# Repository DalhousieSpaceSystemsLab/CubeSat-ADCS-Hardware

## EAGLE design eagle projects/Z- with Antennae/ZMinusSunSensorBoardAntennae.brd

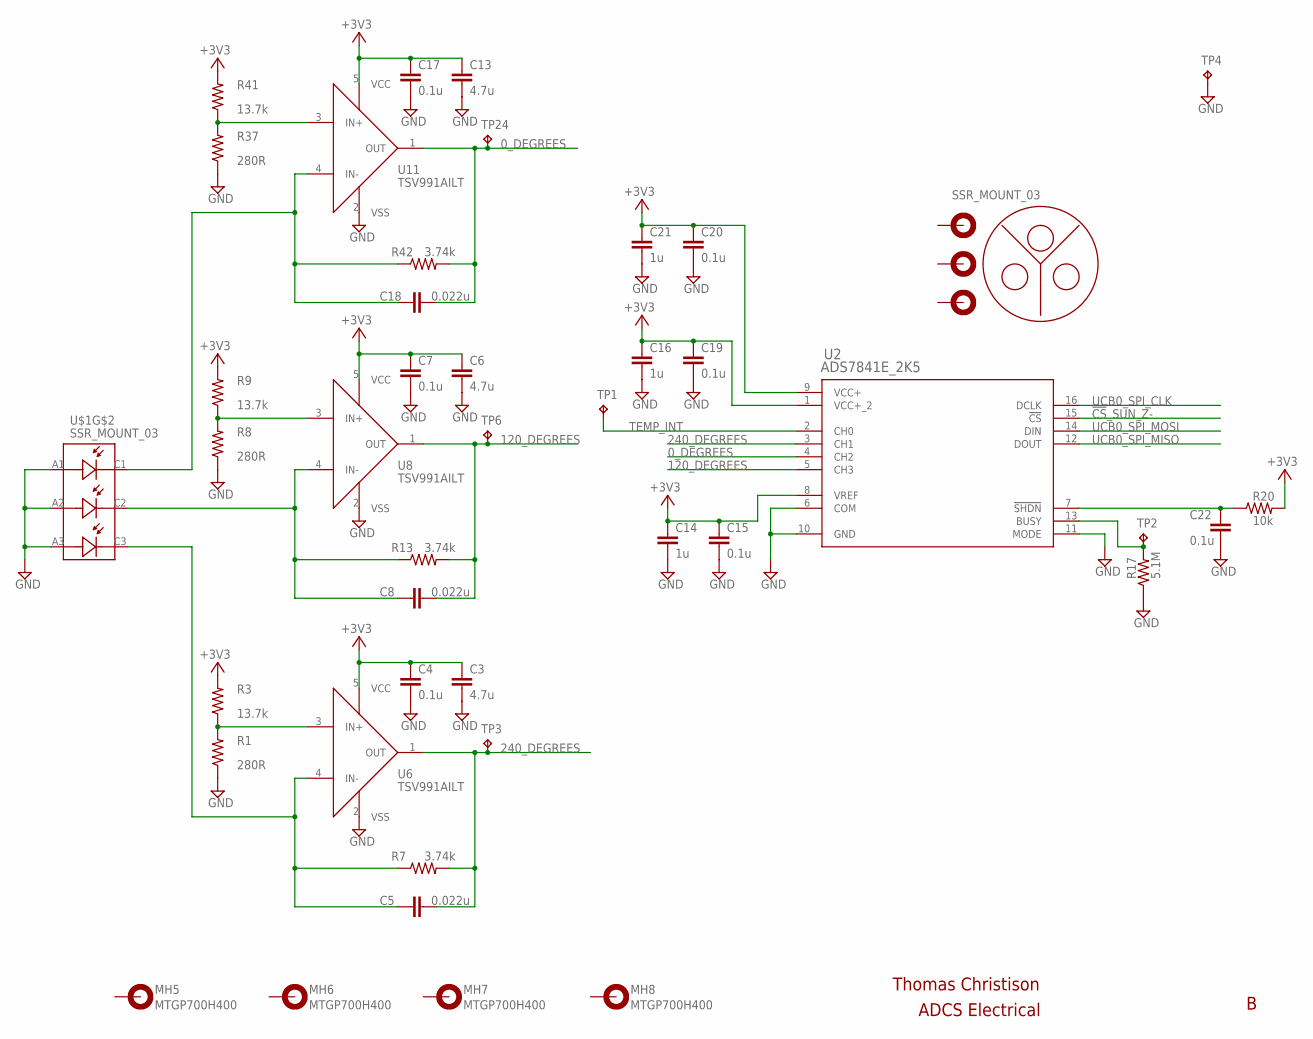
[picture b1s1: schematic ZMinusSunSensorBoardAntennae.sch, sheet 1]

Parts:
C3, C6, C13: 4.7u; C0805
C4, C7, C15, C17, C19, C20, C22: 0.1u; C0402
C5, C8, C18: 0.022u; C0402
C14, C16, C21: 1u; C0402
MH5, MH6, MH7, MH8: MTGP700H400
R1, R8, R37: 280R; R0402
R3, R9, R41: 13.7k; R0402
R7, R13, R42: 3.74k; R0402
R17: 5.1M; R0402
R20: 10k; R0402
TP1, TP2, TP3, TP4, TP6, TP24: TESTPOINT; TP_P76H50
U2: ADS7841E_2K5; DBQ16
U6, U8, U11: TSV991AILT; SOT95P280X145-5N
U$1: SSR_MOUNT_03

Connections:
0_DEGREES: C18.2, R42.2, TP24.1, U2.4 (CH2), U11.1 (OUT)
120_DEGREES: C8.2, R13.2, TP6.1, U2.5 (CH3), U8.1 (OUT)
240_DEGREES: C5.2, R7.2, TP3.1, U2.3 (CH1), U6.1 (OUT)
!CS!_SUN_Z-: U2.15 (!CS); also elsewhere on the board
+3V3: C3.1, C4.1, C6.1, C7.1, C13.1, C14.1, C15.1, C16.1, C17.1, C19.1, C20.1, C21.1, R3.2, R9.2, R20.2, R41.2, U2.1 (VCC+_2), U2.8 (VREF), U2.9 (VCC+), U6.5 (VCC), U8.5 (VCC), U11.5 (VCC); also elsewhere on the board
GND: C3.2, C4.2, C6.2, C7.2, C13.2, C14.2, C15.2, C16.2, C17.2, C19.2, C20.2, C21.2, C22.2, R1.1, R8.1, R17.1, R37.1, TP4.1, U2.6 (COM), U2.10 (GND), U2.11 (MODE), U6.2 (VSS), U8.2 (VSS), U11.2 (VSS), U$1.A1, U$1.A2, U$1.A3; also elsewhere on the board
unnamed: R17.2, TP2.1, U2.13 (BUSY)
unnamed: R1.2, R3.1, U6.3 (IN+)
unnamed: C5.1, R7.1, U6.4 (IN-), U$1.C3
unnamed: C22.1, R20.1, U2.7 (!SHDN)
unnamed: C8.1, R13.1, U8.4 (IN-), U$1.C2
unnamed: R8.2, R9.1, U8.3 (IN+)
unnamed: C18.1, R42.1, U11.4 (IN-), U$1.C1
unnamed: R37.2, R41.1, U11.3 (IN+)
TEMP_INT: TP1.1, U2.2 (CH0); also elsewhere on the board
UCB0_SPI_CLK: U2.16 (DCLK); also elsewhere on the board
UCB0_SPI_MISO: U2.12 (DOUT); also elsewhere on the board
UCB0_SPI_MOSI: U2.14 (DIN); also elsewhere on the board

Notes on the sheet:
Thomas Christison
ADCS Electrical

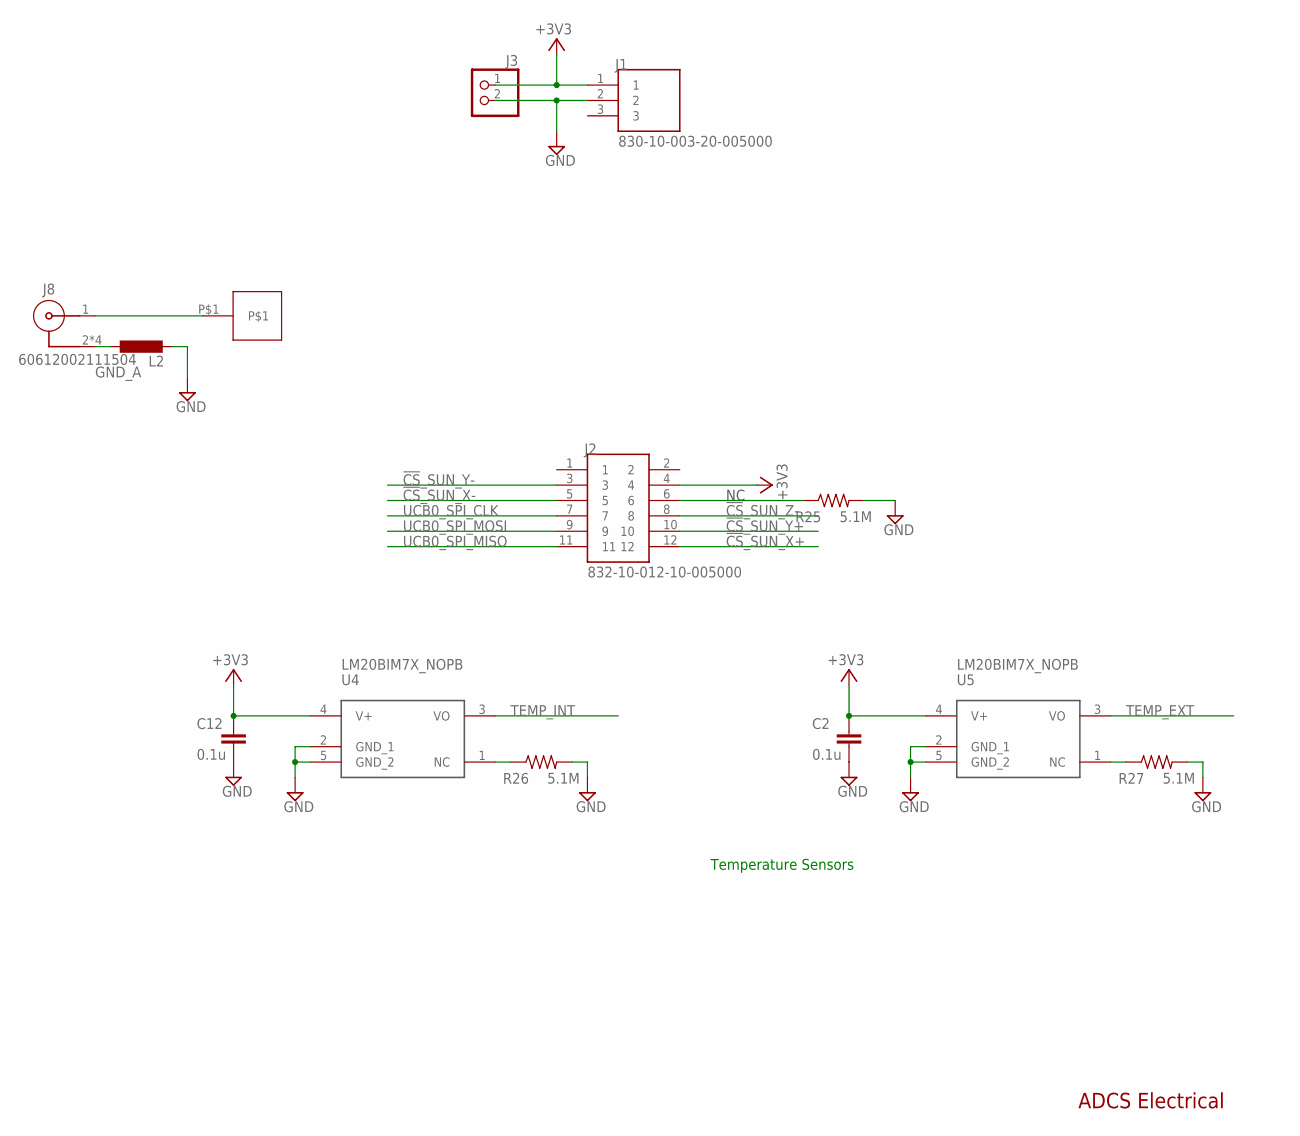
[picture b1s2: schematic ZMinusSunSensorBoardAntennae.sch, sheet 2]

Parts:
C2, C12: 0.1u; C0402
J1: 830-10-003-20-005000
J2: 832-10-012-10-005000
J3: HDR_1X2_; 1X02
J8: 60612002111504
L2: L-EUL5650M; L5650M
R25, R26, R27: 5.1M; R0402
U4, U5: LM20BIM7X_NOPB; SOT23-5P65_210X110L40X22N_LM20
U$2: 2088900001

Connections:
!CS!_SUN_X+: J2.12; also elsewhere on the board
!CS!_SUN_X-: J2.5; also elsewhere on the board
!CS!_SUN_Y+: J2.10; also elsewhere on the board
!CS!_SUN_Y-: J2.3; also elsewhere on the board
!CS!_SUN_Z-: J2.8; also elsewhere on the board
+3V3: C2.1, C12.1, J1.1, J2.4, J3.1, U4.4 (V+), U5.4 (V+); also elsewhere on the board
GND: C2.2, C12.2, J1.2, J3.2, L2.2, R25.2, R26.2, R27.2, U4.2 (GND_1), U4.5 (GND_2), U5.2 (GND_1), U5.5 (GND_2); also elsewhere on the board
GND_A: J8.2, J8.3 (2), J8.4 (2), J8.5 (2), L2.1
unnamed: R26.1, U4.1 (NC)
unnamed: J8.1, U$2.P$1
unnamed: R27.1, U5.1 (NC)
unnamed: J2.6, R25.1
TEMP_EXT: U5.3 (VO); also elsewhere on the board
TEMP_INT: U4.3 (VO); also elsewhere on the board
UCB0_SPI_CLK: J2.7; also elsewhere on the board
UCB0_SPI_MISO: J2.11; also elsewhere on the board
UCB0_SPI_MOSI: J2.9; also elsewhere on the board

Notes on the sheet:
Temperature Sensors
ADCS Electrical

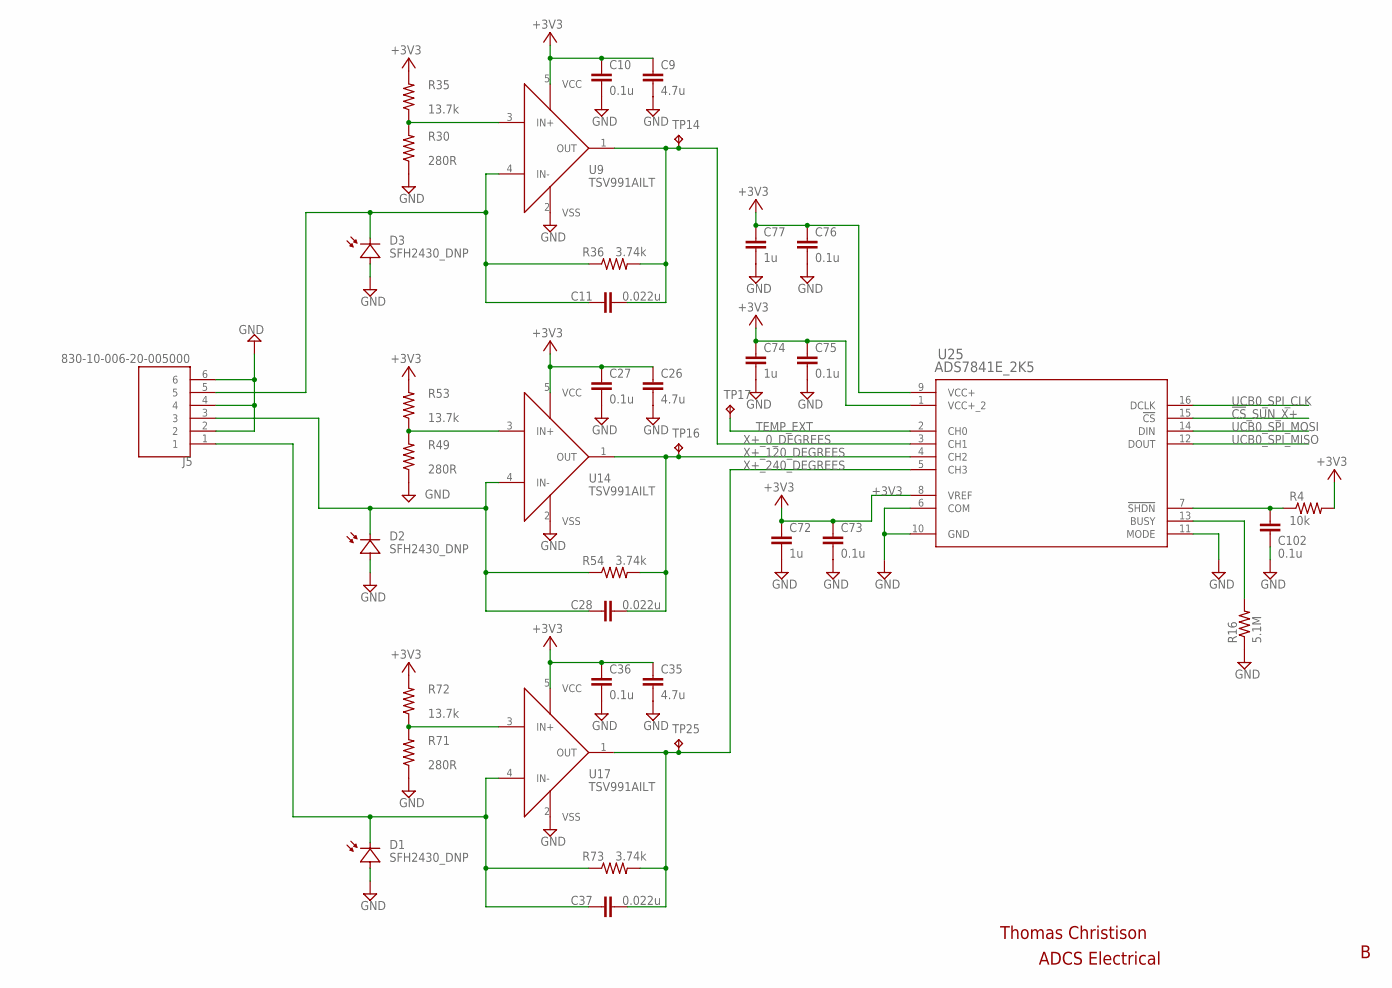
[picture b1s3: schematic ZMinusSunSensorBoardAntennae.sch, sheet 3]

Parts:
C9, C26, C35: 4.7u; C0805
C10, C27, C36, C73, C75, C76, C102: 0.1u; C0402
C11, C28, C37: 0.022u; C0402
C72, C74, C77: 1u; C0402
J5: 830-10-006-20-005000
R4: 10k; R0402
R16: 5.1M; R0402
R30, R49, R71: 280R; R0402
R35, R53, R72: 13.7k; R0402
R36, R54, R73: 3.74k; R0402
TP14, TP16, TP17, TP25: TESTPOINT; TP_P76H50
U9, U14, U17: TSV991AILT; SOT95P280X145-5N
U25: ADS7841E_2K5; DBQ16

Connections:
!CS!_SUN_X+: U25.15 (!CS); also elsewhere on the board
+3V3: C9.1, C10.1, C26.1, C27.1, C35.1, C36.1, C72.1, C73.1, C74.1, C75.1, C76.1, C77.1, R4.2, R35.2, R53.2, R72.2, U9.5 (VCC), U14.5 (VCC), U17.5 (VCC), U25.1 (VCC+_2), U25.8 (VREF), U25.9 (VCC+); also elsewhere on the board
GND: C9.2, C10.2, C26.2, C27.2, C35.2, C36.2, C72.2, C73.2, C74.2, C75.2, C76.2, C77.2, C102.2, J5.2, J5.4, J5.6, R16.1, R30.1, R49.1, R71.1, U9.2 (VSS), U14.2 (VSS), U17.2 (VSS), U25.6 (COM), U25.10 (GND), U25.11 (MODE); also elsewhere on the board
unnamed: C102.1, R4.1, U25.7 (!SHDN)
unnamed: R30.2, R35.1, U9.3 (IN+)
unnamed: C11.1, J5.5, R36.1, U9.4 (IN-)
unnamed: R16.2, U25.13 (BUSY)
unnamed: C28.1, J5.3, R54.1, U14.4 (IN-)
unnamed: C37.1, J5.1, R73.1, U17.4 (IN-)
unnamed: R49.2, R53.1, U14.3 (IN+)
unnamed: R71.2, R72.1, U17.3 (IN+)
TEMP_EXT: TP17.1, U25.2 (CH0); also elsewhere on the board
UCB0_SPI_CLK: U25.16 (DCLK); also elsewhere on the board
UCB0_SPI_MISO: U25.12 (DOUT); also elsewhere on the board
UCB0_SPI_MOSI: U25.14 (DIN); also elsewhere on the board
X+_0_DEGREES: C11.2, R36.2, TP14.1, U9.1 (OUT), U25.3 (CH1)
X+_120_DEGREES: C28.2, R54.2, TP16.1, U14.1 (OUT), U25.4 (CH2)
X+_240_DEGREES: C37.2, R73.2, TP25.1, U17.1 (OUT), U25.5 (CH3)

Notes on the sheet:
Thomas Christison
ADCS Electrical

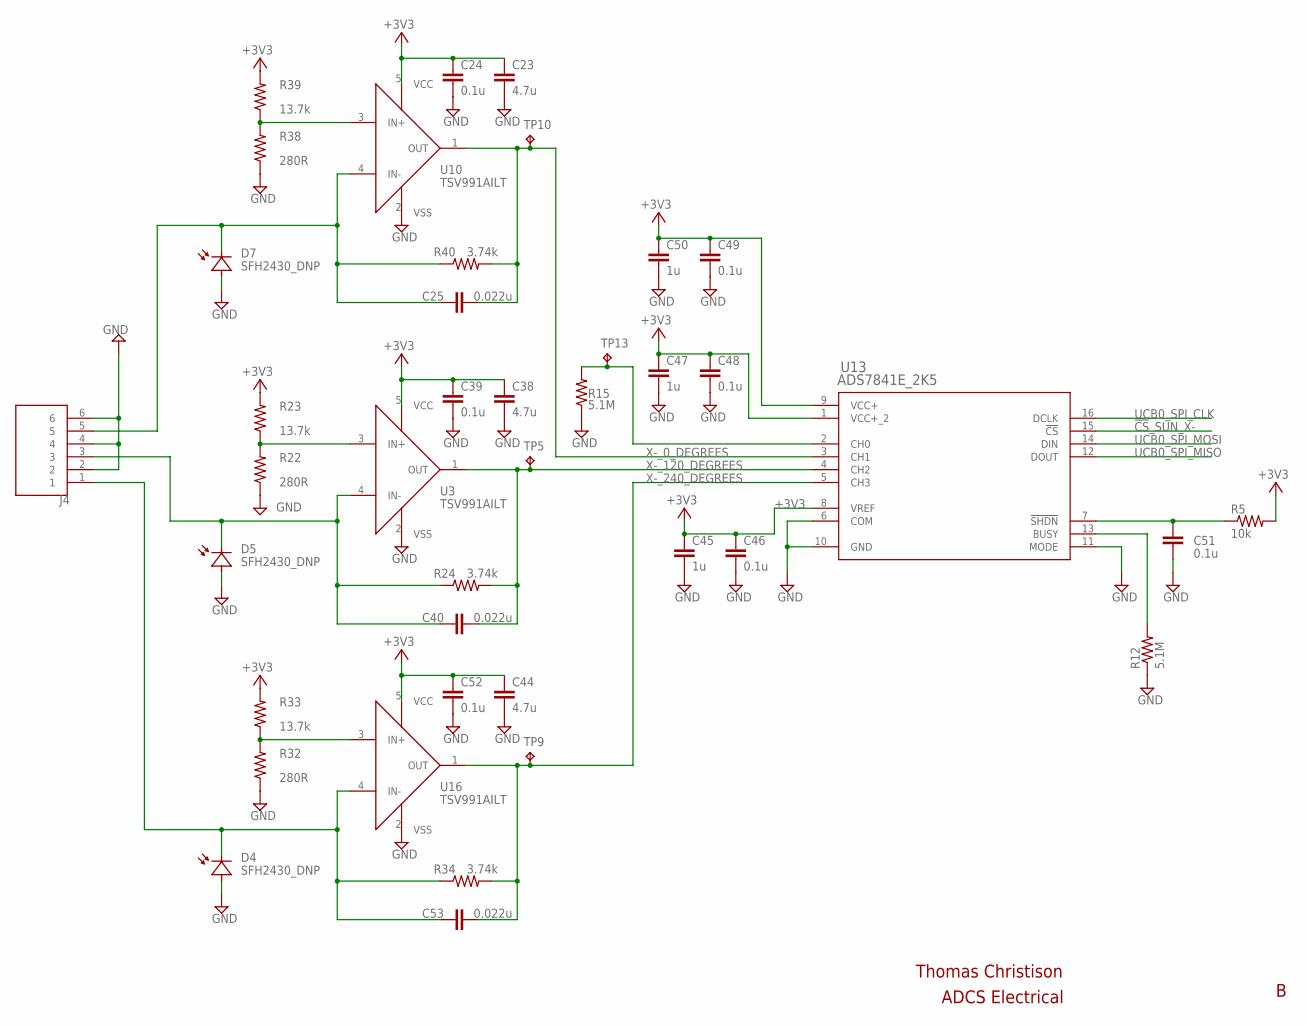
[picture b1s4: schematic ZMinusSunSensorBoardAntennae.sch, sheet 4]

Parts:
C23, C38, C44: 4.7u; C0805
C24, C39, C46, C48, C49, C51, C52: 0.1u; C0402
C25, C40, C53: 0.022u; C0402
C45, C47, C50: 1u; C0402
J4: 830-10-006-20-005000
R5: 10k; R0402
R12, R15: 5.1M; R0402
R22, R32, R38: 280R; R0402
R23, R33, R39: 13.7k; R0402
R24, R34, R40: 3.74k; R0402
TP5, TP9, TP10, TP13: TESTPOINT; TP_P76H50
U3, U10, U16: TSV991AILT; SOT95P280X145-5N
U13: ADS7841E_2K5; DBQ16

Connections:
!CS!_SUN_X-: U13.15 (!CS); also elsewhere on the board
+3V3: C23.1, C24.1, C38.1, C39.1, C44.1, C45.1, C46.1, C47.1, C48.1, C49.1, C50.1, C52.1, R5.2, R23.2, R33.2, R39.2, U3.5 (VCC), U10.5 (VCC), U13.1 (VCC+_2), U13.8 (VREF), U13.9 (VCC+), U16.5 (VCC); also elsewhere on the board
GND: C23.2, C24.2, C38.2, C39.2, C44.2, C45.2, C46.2, C47.2, C48.2, C49.2, C50.2, C51.2, C52.2, J4.2, J4.4, J4.6, R12.1, R15.1, R22.1, R32.1, R38.1, U3.2 (VSS), U10.2 (VSS), U13.6 (COM), U13.10 (GND), U13.11 (MODE), U16.2 (VSS); also elsewhere on the board
unnamed: R38.2, R39.1, U10.3 (IN+)
unnamed: R15.2, TP13.1, U13.2 (CH0)
unnamed: C51.1, R5.1, U13.7 (!SHDN)
unnamed: R22.2, R23.1, U3.3 (IN+)
unnamed: C25.1, J4.5, R40.1, U10.4 (IN-)
unnamed: R32.2, R33.1, U16.3 (IN+)
unnamed: C40.1, J4.3, R24.1, U3.4 (IN-)
unnamed: C53.1, J4.1, R34.1, U16.4 (IN-)
unnamed: R12.2, U13.13 (BUSY)
UCB0_SPI_CLK: U13.16 (DCLK); also elsewhere on the board
UCB0_SPI_MISO: U13.12 (DOUT); also elsewhere on the board
UCB0_SPI_MOSI: U13.14 (DIN); also elsewhere on the board
X-_0_DEGREES: C25.2, R40.2, TP10.1, U10.1 (OUT), U13.3 (CH1)
X-_120_DEGREES: C40.2, R24.2, TP5.1, U3.1 (OUT), U13.4 (CH2)
X-_240_DEGREES: C53.2, R34.2, TP9.1, U13.5 (CH3), U16.1 (OUT)

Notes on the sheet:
Thomas Christison
ADCS Electrical

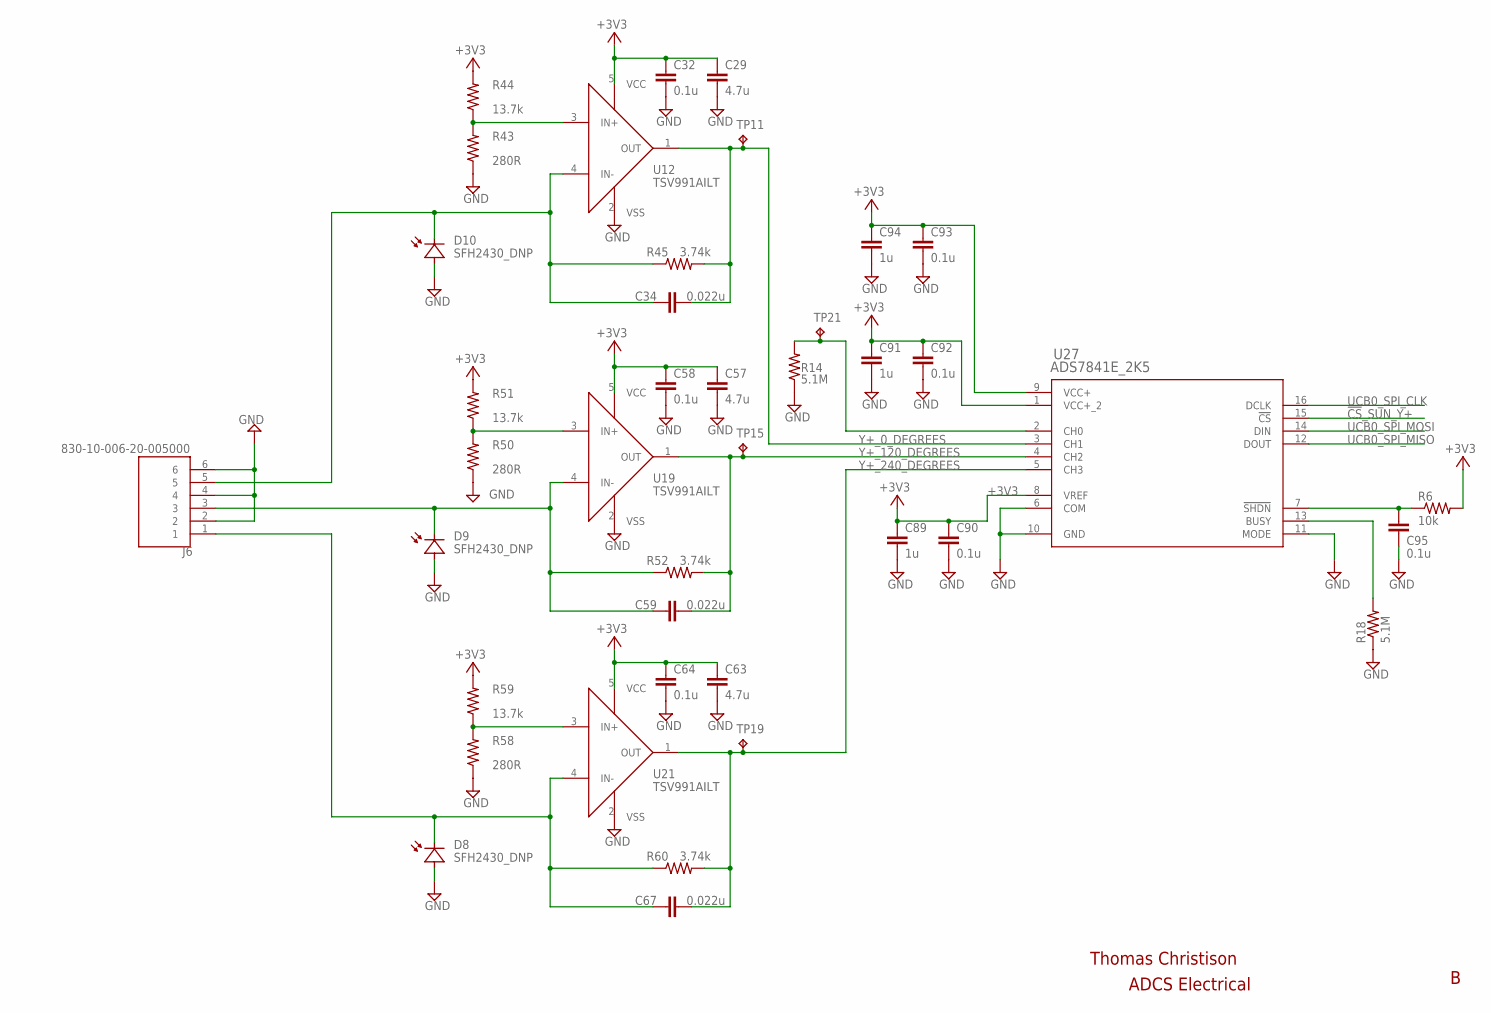
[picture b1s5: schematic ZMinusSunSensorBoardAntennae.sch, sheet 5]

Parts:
C29, C57, C63: 4.7u; C0805
C32, C58, C64, C90, C92, C93, C95: 0.1u; C0402
C34, C59, C67: 0.022u; C0402
C89, C91, C94: 1u; C0402
J6: 830-10-006-20-005000
R6: 10k; R0402
R14, R18: 5.1M; R0402
R43, R50, R58: 280R; R0402
R44, R51, R59: 13.7k; R0402
R45, R52, R60: 3.74k; R0402
TP11, TP15, TP19, TP21: TESTPOINT; TP_P76H50
U12, U19, U21: TSV991AILT; SOT95P280X145-5N
U27: ADS7841E_2K5; DBQ16

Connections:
!CS!_SUN_Y+: U27.15 (!CS); also elsewhere on the board
+3V3: C29.1, C32.1, C57.1, C58.1, C63.1, C64.1, C89.1, C90.1, C91.1, C92.1, C93.1, C94.1, R6.2, R44.2, R51.2, R59.2, U12.5 (VCC), U19.5 (VCC), U21.5 (VCC), U27.1 (VCC+_2), U27.8 (VREF), U27.9 (VCC+); also elsewhere on the board
GND: C29.2, C32.2, C57.2, C58.2, C63.2, C64.2, C89.2, C90.2, C91.2, C92.2, C93.2, C94.2, C95.2, J6.2, J6.4, J6.6, R14.1, R18.1, R43.1, R50.1, R58.1, U12.2 (VSS), U19.2 (VSS), U21.2 (VSS), U27.6 (COM), U27.10 (GND), U27.11 (MODE); also elsewhere on the board
unnamed: C34.1, J6.5, R45.1, U12.4 (IN-)
unnamed: C59.1, J6.3, R52.1, U19.4 (IN-)
unnamed: R14.2, TP21.1, U27.2 (CH0)
unnamed: C95.1, R6.1, U27.7 (!SHDN)
unnamed: R43.2, R44.1, U12.3 (IN+)
unnamed: R18.2, U27.13 (BUSY)
unnamed: R50.2, R51.1, U19.3 (IN+)
unnamed: R58.2, R59.1, U21.3 (IN+)
unnamed: C67.1, J6.1, R60.1, U21.4 (IN-)
UCB0_SPI_CLK: U27.16 (DCLK); also elsewhere on the board
UCB0_SPI_MISO: U27.12 (DOUT); also elsewhere on the board
UCB0_SPI_MOSI: U27.14 (DIN); also elsewhere on the board
Y+_0_DEGREES: C34.2, R45.2, TP11.1, U12.1 (OUT), U27.3 (CH1)
Y+_120_DEGREES: C59.2, R52.2, TP15.1, U19.1 (OUT), U27.4 (CH2)
Y+_240_DEGREES: C67.2, R60.2, TP19.1, U21.1 (OUT), U27.5 (CH3)

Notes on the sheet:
Thomas Christison
ADCS Electrical

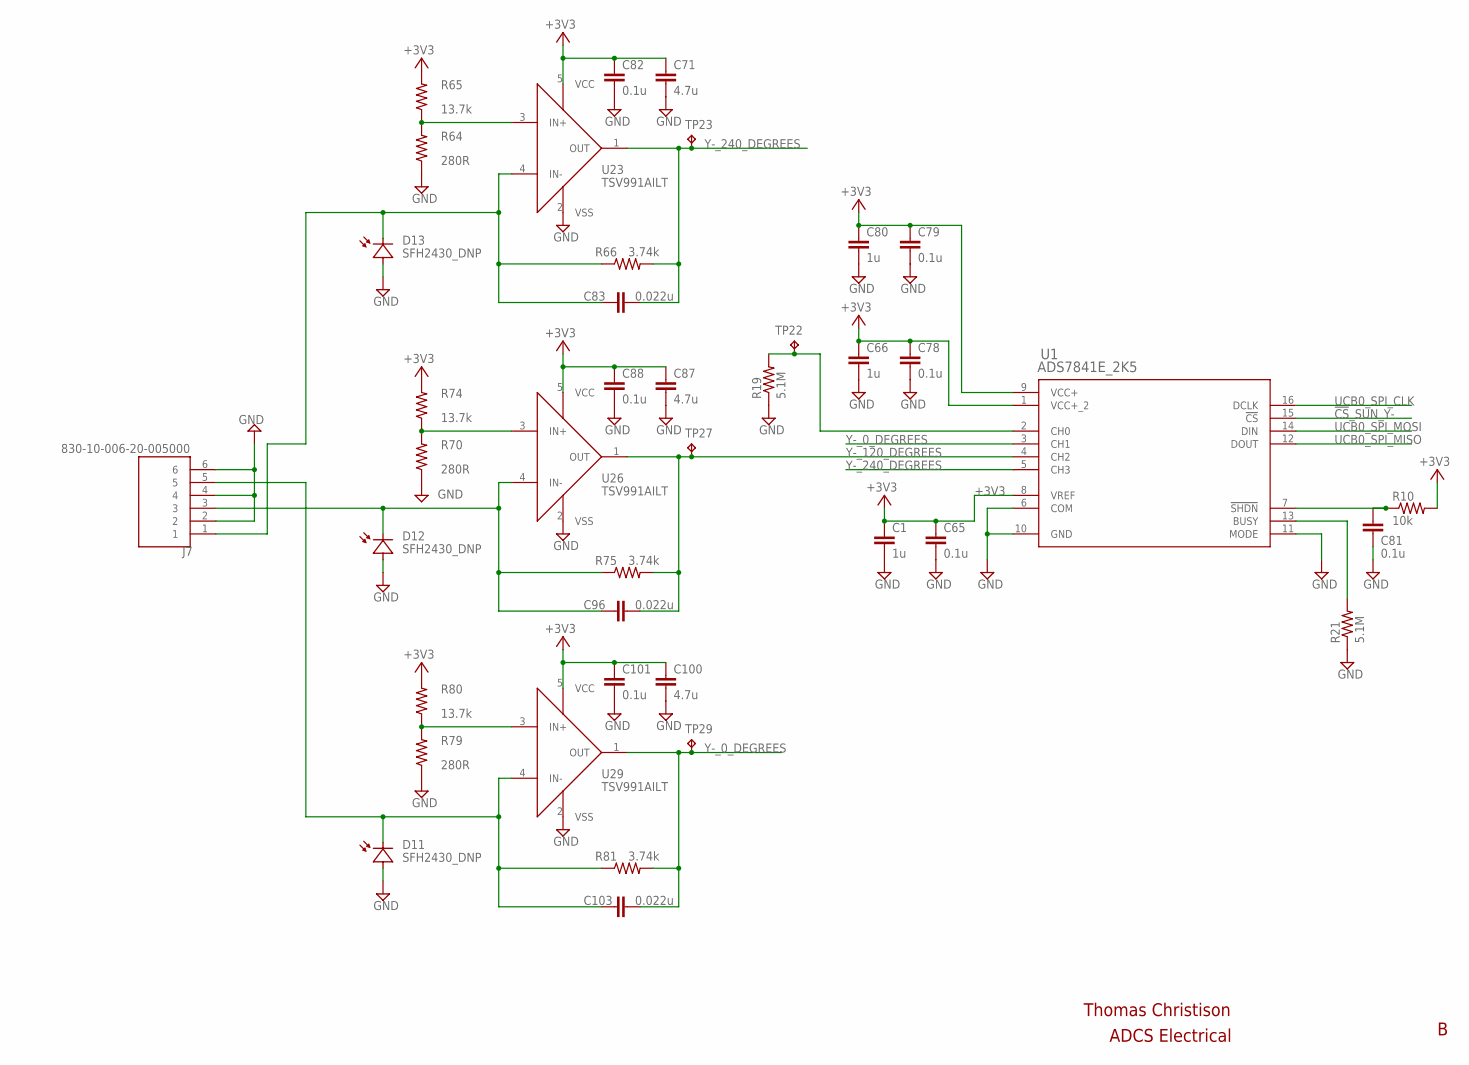
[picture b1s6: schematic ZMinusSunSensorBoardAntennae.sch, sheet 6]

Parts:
C1, C66, C80: 1u; C0402
C65, C78, C79, C81, C82, C88, C101: 0.1u; C0402
C71, C87, C100: 4.7u; C0805
C83, C96, C103: 0.022u; C0402
J7: 830-10-006-20-005000
R10: 10k; R0402
R19, R21: 5.1M; R0402
R64, R70, R79: 280R; R0402
R65, R74, R80: 13.7k; R0402
R66, R75, R81: 3.74k; R0402
TP22, TP23, TP27, TP29: TESTPOINT; TP_P76H50
U1: ADS7841E_2K5; DBQ16
U23, U26, U29: TSV991AILT; SOT95P280X145-5N

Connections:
!CS!_SUN_Y-: U1.15 (!CS); also elsewhere on the board
+3V3: C1.1, C65.1, C66.1, C71.1, C78.1, C79.1, C80.1, C82.1, C87.1, C88.1, C100.1, C101.1, R10.2, R65.2, R74.2, R80.2, U1.1 (VCC+_2), U1.8 (VREF), U1.9 (VCC+), U23.5 (VCC), U26.5 (VCC), U29.5 (VCC); also elsewhere on the board
GND: C1.2, C65.2, C66.2, C71.2, C78.2, C79.2, C80.2, C81.2, C82.2, C87.2, C88.2, C100.2, C101.2, J7.2, J7.4, J7.6, R19.1, R21.1, R64.1, R70.1, R79.1, U1.6 (COM), U1.10 (GND), U1.11 (MODE), U23.2 (VSS), U26.2 (VSS), U29.2 (VSS); also elsewhere on the board
unnamed: C96.1, J7.3, R75.1, U26.4 (IN-)
unnamed: R19.2, TP22.1, U1.2 (CH0)
unnamed: C103.1, J7.5, R81.1, U29.4 (IN-)
unnamed: C81.1, R10.1, U1.7 (!SHDN)
unnamed: C83.1, J7.1, R66.1, U23.4 (IN-)
unnamed: R21.2, U1.13 (BUSY)
unnamed: R64.2, R65.1, U23.3 (IN+)
unnamed: R70.2, R74.1, U26.3 (IN+)
unnamed: R79.2, R80.1, U29.3 (IN+)
UCB0_SPI_CLK: U1.16 (DCLK); also elsewhere on the board
UCB0_SPI_MISO: U1.12 (DOUT); also elsewhere on the board
UCB0_SPI_MOSI: U1.14 (DIN); also elsewhere on the board
Y-_0_DEGREES: C103.2, R81.2, TP29.1, U1.3 (CH1), U29.1 (OUT)
Y-_120_DEGREES: C96.2, R75.2, TP27.1, U1.4 (CH2), U26.1 (OUT)
Y-_240_DEGREES: C83.2, R66.2, TP23.1, U1.5 (CH3), U23.1 (OUT)

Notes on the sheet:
Thomas Christison
ADCS Electrical

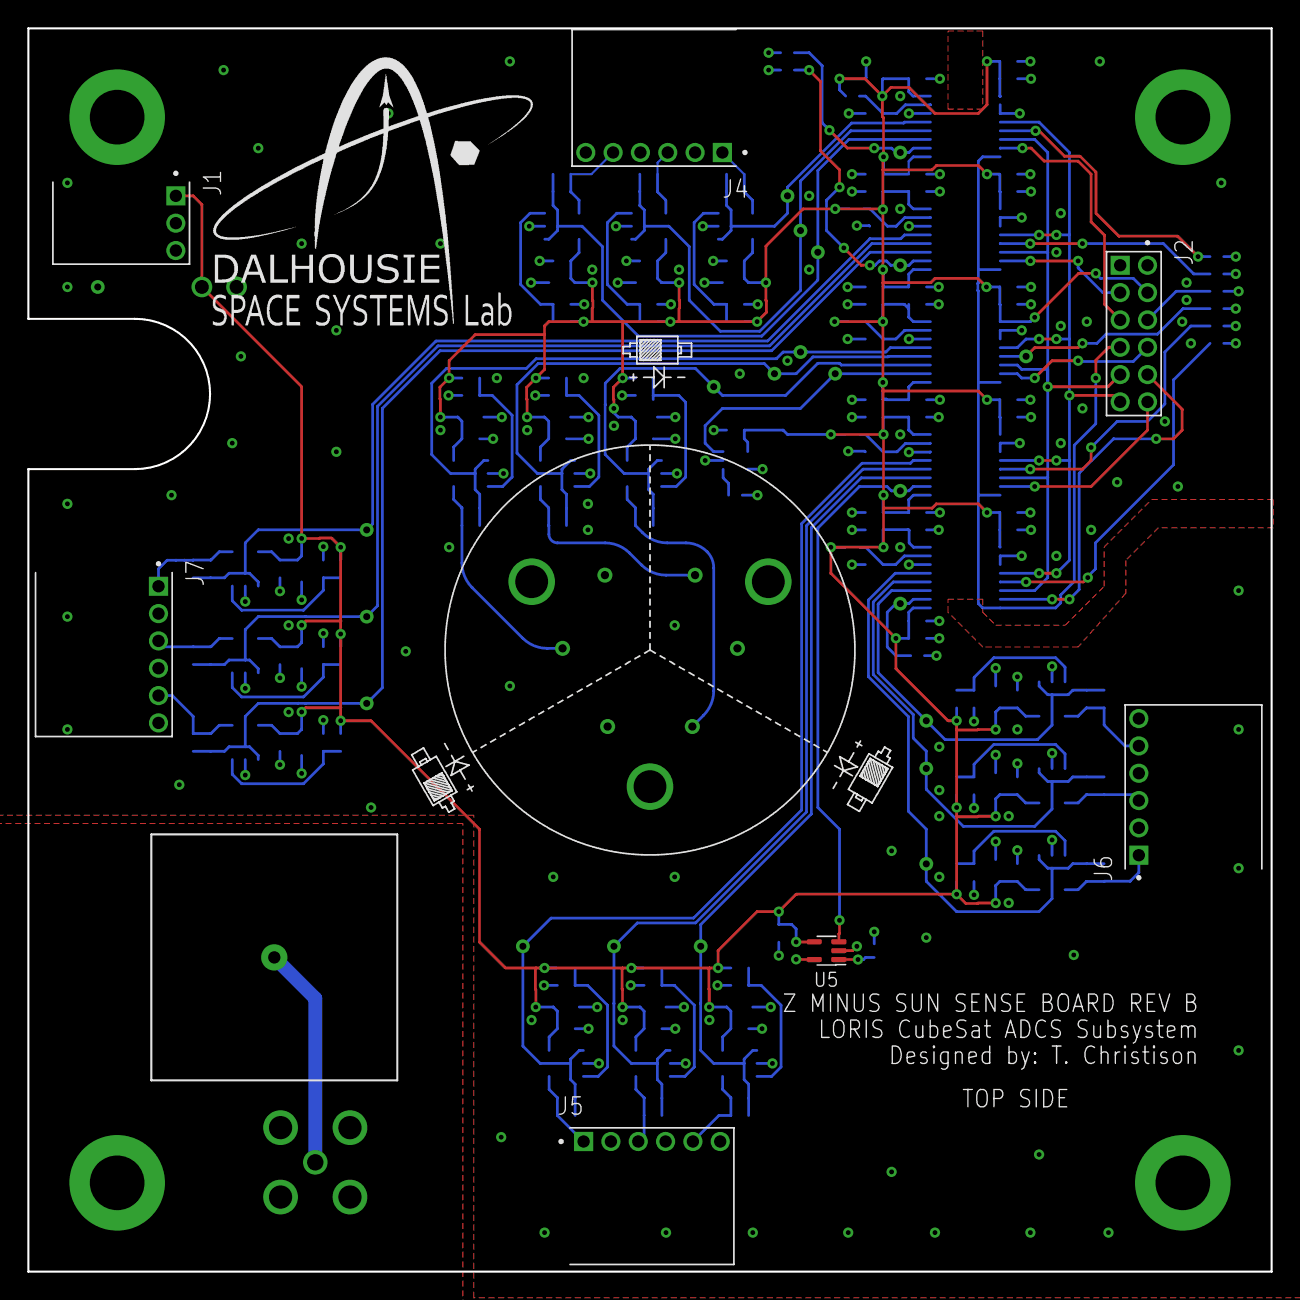
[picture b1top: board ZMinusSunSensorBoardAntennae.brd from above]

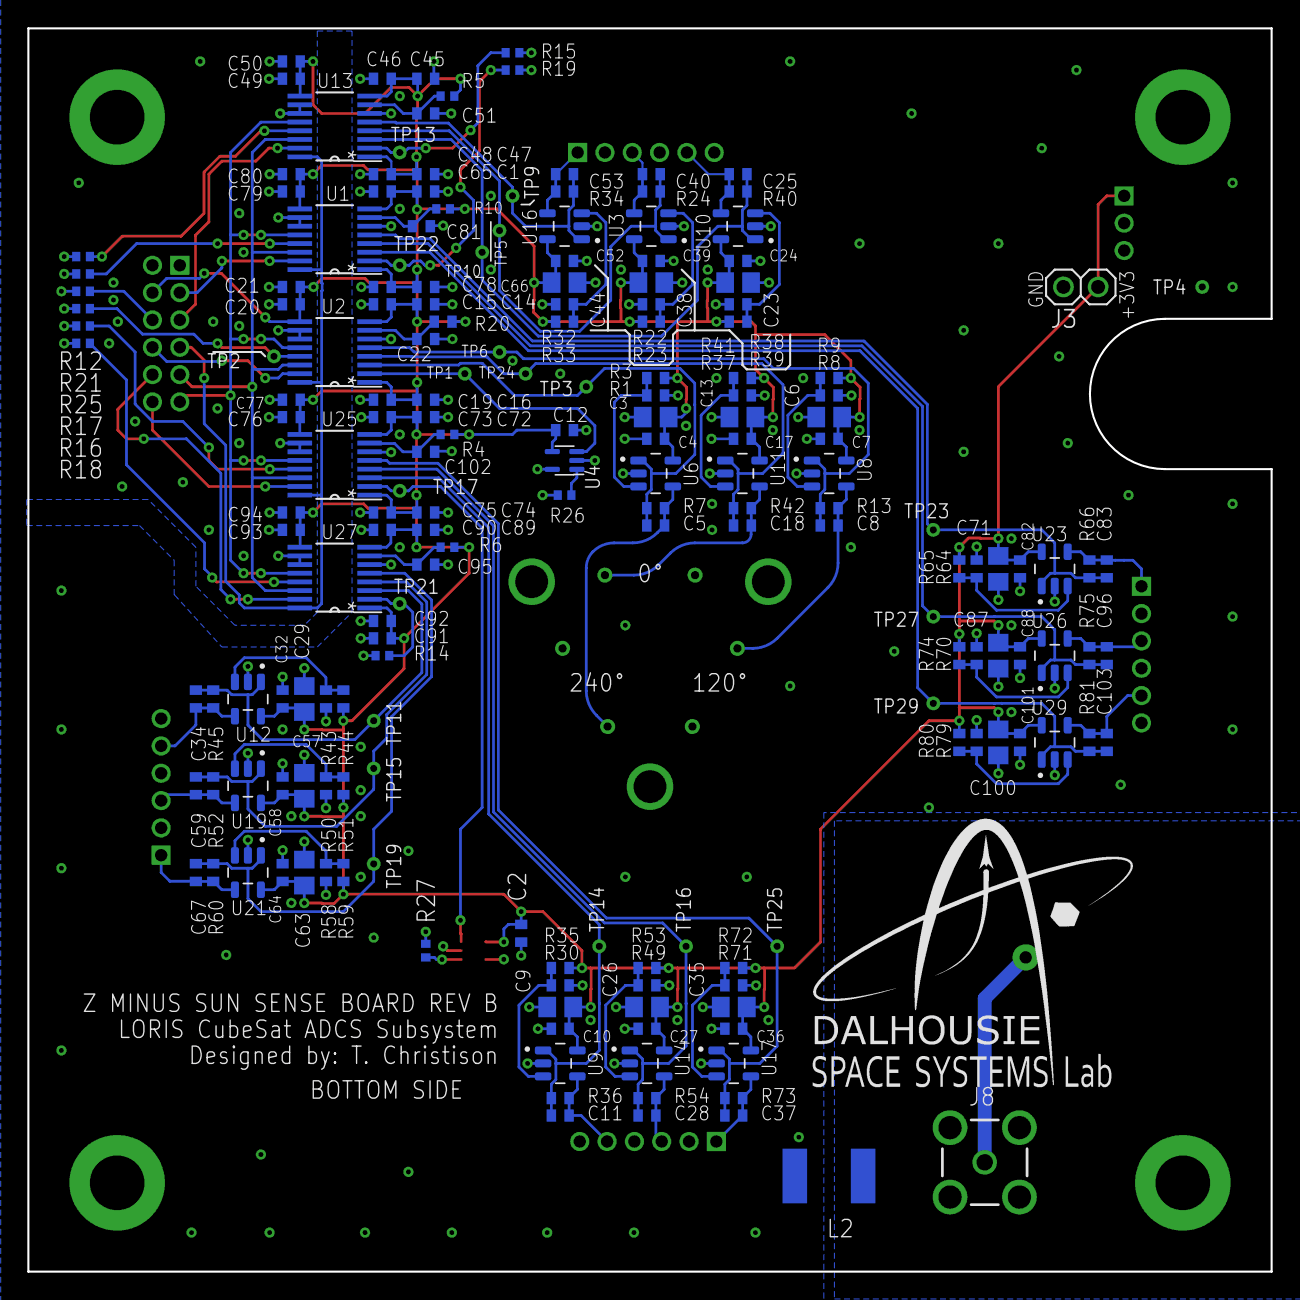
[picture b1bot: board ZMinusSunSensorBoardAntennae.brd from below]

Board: 2 copper layers, 91.0 x 91.0 mm, 205 parts (189 on the bottom side), 75 nets.

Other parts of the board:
U$3, U$4, U$5: PHOTODIODE_SILK

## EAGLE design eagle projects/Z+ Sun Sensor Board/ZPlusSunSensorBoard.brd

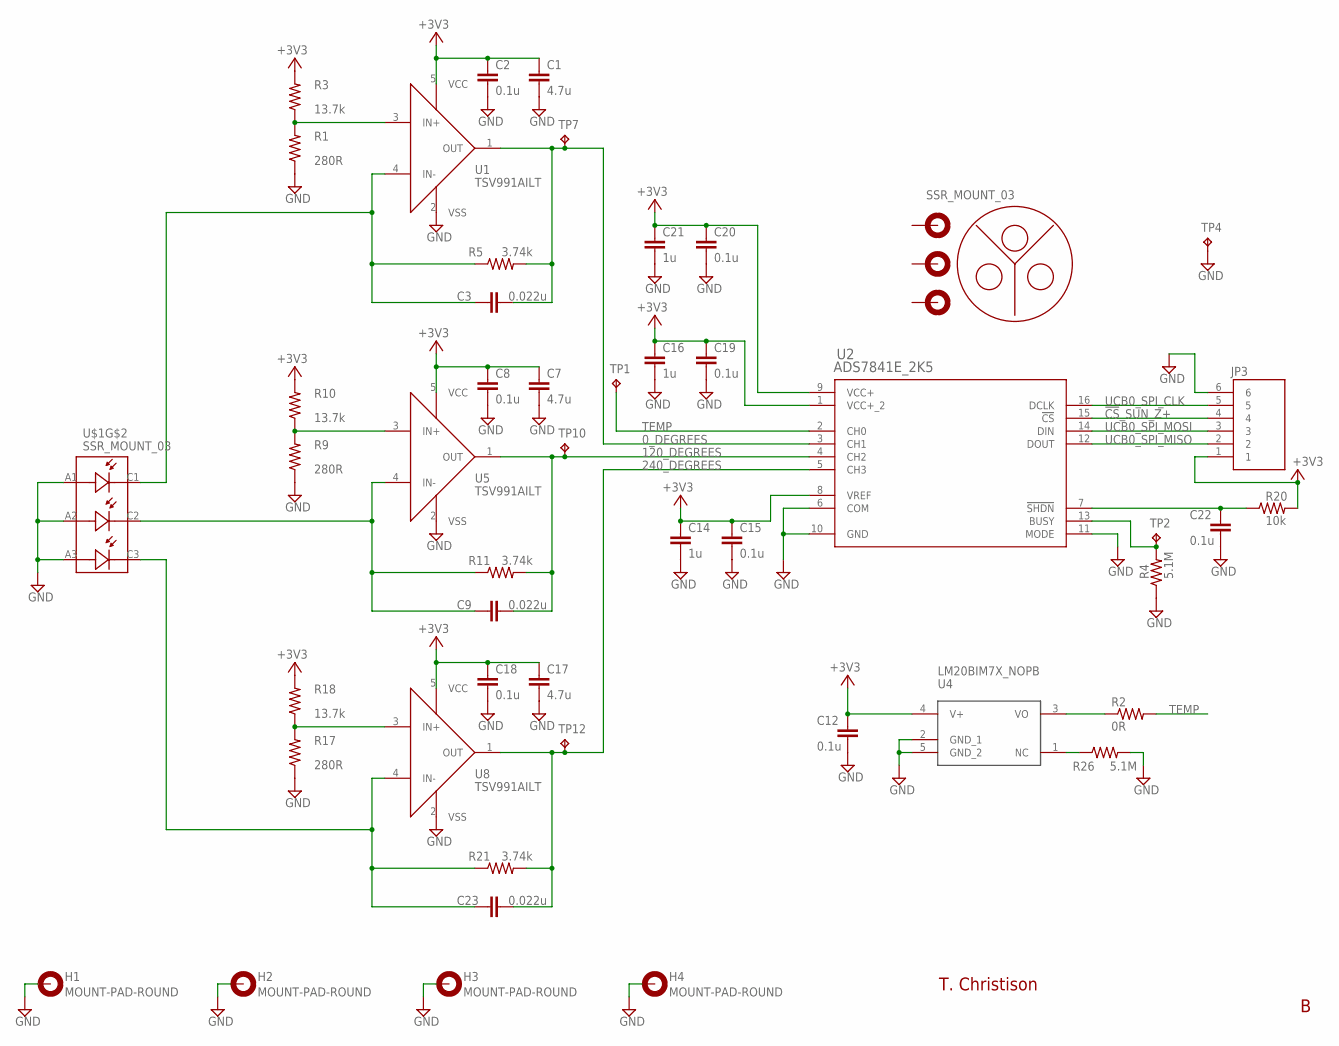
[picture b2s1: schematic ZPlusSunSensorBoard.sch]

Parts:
C1, C7, C17: 4.7u; C0805
C2, C8, C12, C15, C18, C19, C20, C22: 0.1u; C0402
C3, C9, C23: 0.022u; C0402
C14, C16, C21: 1u; C0402
H1, H2, H3, H4: MOUNT-PAD-ROUND; PC104
JP3: 830-10-006-20-005000
R1, R9, R17: 280R; R0402
R2: 0R; R0805
R3, R10, R18: 13.7k; R0402
R4, R26: 5.1M; R0402
R5, R11, R21: 3.74k; R0402
R20: 10k; R0402
TP1, TP2, TP4, TP7, TP10, TP12: TESTPOINT; TP_P76H50
U1, U5, U8: TSV991AILT; SOT95P280X145-5N
U2: ADS7841E_2K5; DBQ16
U4: LM20BIM7X_NOPB; SOT23-5P65_210X110L40X22N_LM20
U$1: SSR_MOUNT_03

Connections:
0_DEGREES: C3.2, R5.2, TP7.1, U1.1 (OUT), U2.3 (CH1)
120_DEGREES: C9.2, R11.2, TP10.1, U2.4 (CH2), U5.1 (OUT)
240_DEGREES: C23.2, R21.2, TP12.1, U2.5 (CH3), U8.1 (OUT)
!CS!_SUN_Z+: JP3.4, U2.15 (!CS)
+3V3: C1.1, C2.1, C7.1, C8.1, C12.1, C14.1, C15.1, C16.1, C17.1, C18.1, C19.1, C20.1, C21.1, JP3.1, R3.2, R10.2, R18.2, R20.2, U1.5 (VCC), U2.1 (VCC+_2), U2.8 (VREF), U2.9 (VCC+), U4.4 (V+), U5.5 (VCC), U8.5 (VCC)
GND: C1.2, C2.2, C7.2, C8.2, C12.2, C14.2, C15.2, C16.2, C17.2, C18.2, C19.2, C20.2, C21.2, C22.2, H1.B3,15, H2.B3,15, H3.B3,15, H4.B3,15, JP3.6, R1.1, R4.1, R9.1, R17.1, R26.2, TP4.1, U1.2 (VSS), U2.6 (COM), U2.10 (GND), U2.11 (MODE), U4.2 (GND_1), U4.5 (GND_2), U5.2 (VSS), U8.2 (VSS), U$1.A1, U$1.A2, U$1.A3
unnamed: R2.1, U4.3 (VO)
unnamed: R4.2, TP2.1, U2.13 (BUSY)
unnamed: C3.1, R5.1, U1.4 (IN-), U$1.C1
unnamed: R26.1, U4.1 (NC)
unnamed: R1.2, R3.1, U1.3 (IN+)
unnamed: C9.1, R11.1, U5.4 (IN-), U$1.C2
unnamed: C23.1, R21.1, U8.4 (IN-), U$1.C3
unnamed: R9.2, R10.1, U5.3 (IN+)
unnamed: C22.1, R20.1, U2.7 (!SHDN)
unnamed: R17.2, R18.1, U8.3 (IN+)
TEMP: R2.2, TP1.1, U2.2 (CH0)
UCB0_SPI_CLK: JP3.5, U2.16 (DCLK)
UCB0_SPI_MISO: JP3.2, U2.12 (DOUT)
UCB0_SPI_MOSI: JP3.3, U2.14 (DIN)

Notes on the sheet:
T. Christison
